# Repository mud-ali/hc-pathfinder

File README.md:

# pathfinder submission

i made a little ring of LEDs, with buttons to control the light sequence that appears on them

# pictures of PCB

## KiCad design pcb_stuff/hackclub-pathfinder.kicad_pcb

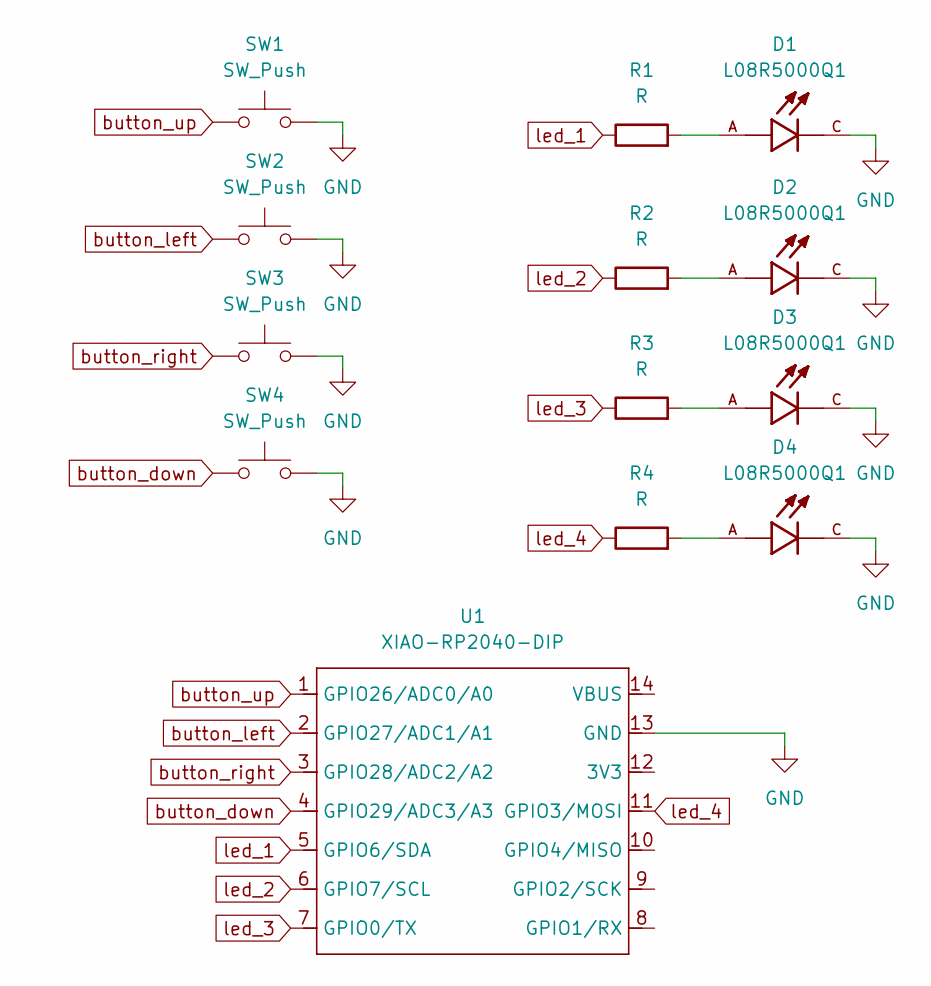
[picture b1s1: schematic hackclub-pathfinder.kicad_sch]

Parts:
D1, D2, D3, D4: L08R5000Q1; LEDRD254W57D500H1070; PARTREV NA
R1, R2, R3, R4: R; R_Axial_DIN0204_L3.6mm_D1.6mm_P5.08mm_Horizontal
SW1, SW2, SW3, SW4: SW_Push; SW_Cherry_MX_1.00u_PCB
U1: XIAO-RP2040-DIP

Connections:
GND: D1.C, D2.C, D3.C, D4.C, SW1.2, SW2.2, SW3.2, SW4.2, U1.13 (GND)
unnamed: D1.A, R1.2
unnamed: D2.A, R2.2
unnamed: D3.A, R3.2
unnamed: D4.A, R4.2
button_down: SW4.1, U1.4 (GPIO29/ADC3/A3)
button_left: SW2.1, U1.2 (GPIO27/ADC1/A1)
button_right: SW3.1, U1.3 (GPIO28/ADC2/A2)
button_up: SW1.1, U1.1 (GPIO26/ADC0/A0)
led_1: R1.1, U1.5 (GPIO6/SDA)
led_2: R2.1, U1.6 (GPIO7/SCL)
led_3: R3.1, U1.7 (GPIO0/TX)
led_4: R4.1, U1.11 (GPIO3/MOSI)

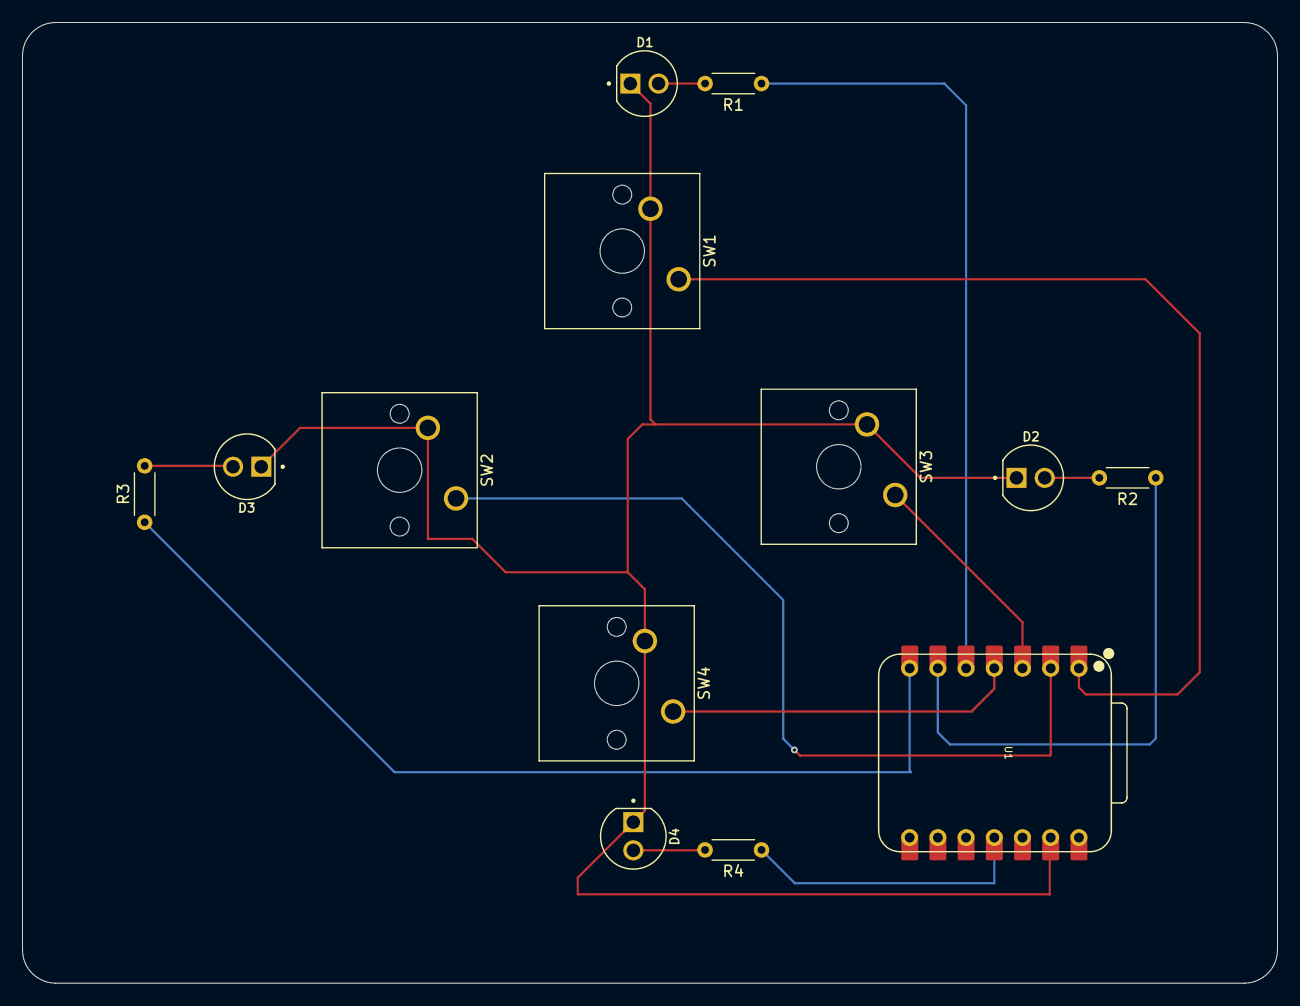
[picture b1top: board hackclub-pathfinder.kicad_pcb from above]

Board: 2 copper layers, 113.0 x 86.5 mm, 13 parts (0 on the bottom side), 13 nets.

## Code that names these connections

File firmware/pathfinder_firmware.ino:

const int led_top = 5;
const int led_right = 6;
const int led_bottom = 11;
const int led_left = 7;

const int button_up = 1;
const int button_right = 3;
const int button_down = 4;
const int button_left = 2;

int delayDuration = 500;
int direction = 1; // clockwise

int led_order[] = {5, 6, 7, 11};
int LED_COUNT = 4;

int current_led = 0;
unsigned long last_time = 0;

void setup() {
  pinMode(led_bottom, OUTPUT);
  pinMode(led_top, OUTPUT);
  pinMode(led_right, OUTPUT);
  pinMode(led_left, OUTPUT);

  pinMode(button_up, INPUT_PULLUP);
  pinMode(button_down, INPUT_PULLUP);
  pinMode(button_left, INPUT_PULLUP);
  pinMode(button_right, INPUT_PULLUP);

  last_time = millis();
}

void loop() {
  if (digitalRead(button_down)) delayDuration = min(delayDuration+100, 1000);
  else if (digitalRead(button_up)) delayDuration = max(delayDuration-100, 100);

  if (digitalRead(button_left)) direction = -1;
  else if (digitalRead(button_right)) direction = 1;

  digitalWrite(led_order[current_led], HIGH);

  if (millis() >= last_time + delayDuration) {
    digitalWrite(led_order[current_led], LOW);
    current_led = get_next_led_index(current_led);
    last_time = millis();
  }
}

int get_next_led_index(int current_index) {
  return (current_index+direction) % LED_COUNT;
}
